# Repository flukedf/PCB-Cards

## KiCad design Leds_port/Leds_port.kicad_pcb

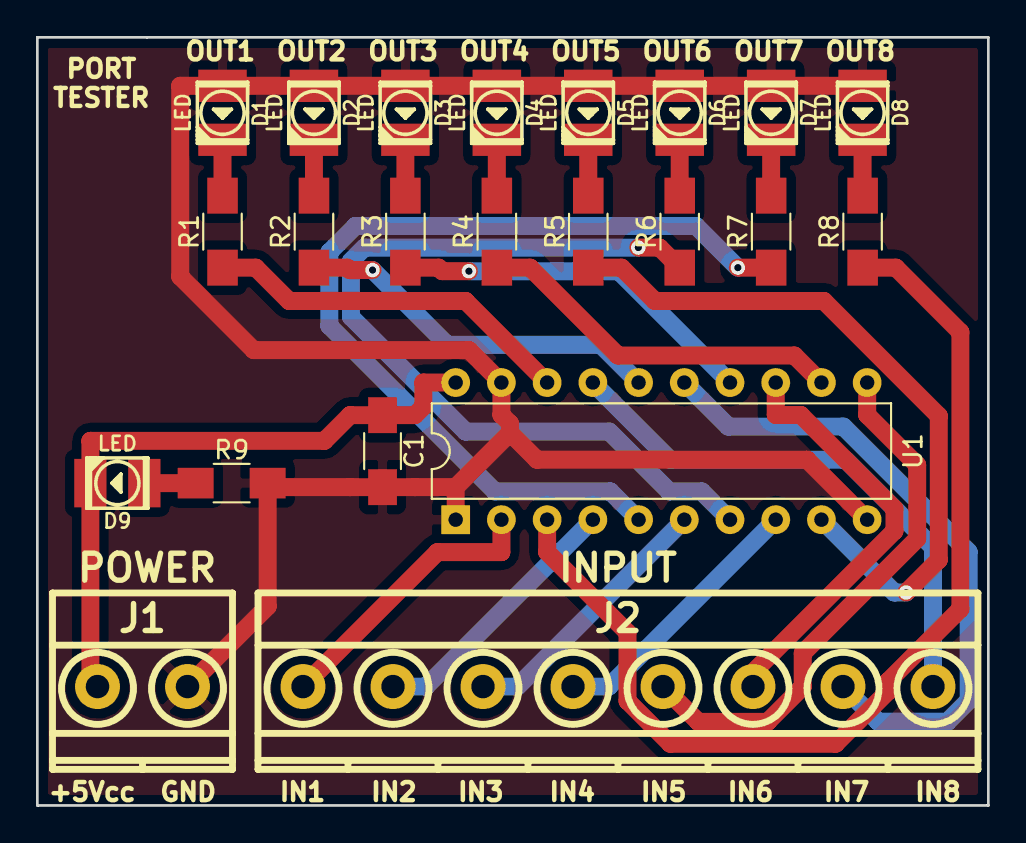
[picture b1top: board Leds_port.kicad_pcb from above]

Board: 2 copper layers, 52.8 x 42.7 mm, 22 parts (0 on the bottom side), 27 nets.

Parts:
C1: 100nF; C_1206_HandSoldering
D1, D2, D3, D4, D5, D6, D7, D8, D9: LED; Led_PLCC2_3528
J1: POWER; mkds_1,5-2
J2: INPUT; mkds_1,5-8
R1, R2, R3, R4, R5, R6, R7, R8, R9: 330; R_1206_HandSoldering
U1: 74LS244; DIP-20_W7.62mm

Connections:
+5Vcc: C1.1, D9.2, J1.1, U1.20
GND: C1.2, D1.1, D2.1, D3.1, D4.1, D5.1, D6.1, D7.1, D8.1, J1.2, R9.2, U1.1, U1.10, U1.19
IN01: J2.1, U1.2
IN02: J2.2, U1.4
IN03: J2.3, U1.6
IN04: J2.4, U1.8
IN05: J2.5, U1.11
IN06: J2.6, U1.13
IN07: J2.7, U1.15
IN08: J2.8, U1.17
unnamed: D1.2, R1.2
unnamed: D2.2, R2.2
unnamed: D3.2, R3.2
unnamed: D4.2, R4.2
unnamed: D5.2, R5.2
unnamed: D6.2, R6.2
unnamed: D7.2, R7.2
unnamed: D8.2, R8.2
unnamed: D9.1, R9.1
S1: R1.1, U1.18
S2: R2.1, U1.16
S3: R3.1, U1.14
S4: R4.1, U1.12
S5: R5.1, U1.9
S6: R6.1, U1.7
S7: R7.1, U1.5
S8: R8.1, U1.3

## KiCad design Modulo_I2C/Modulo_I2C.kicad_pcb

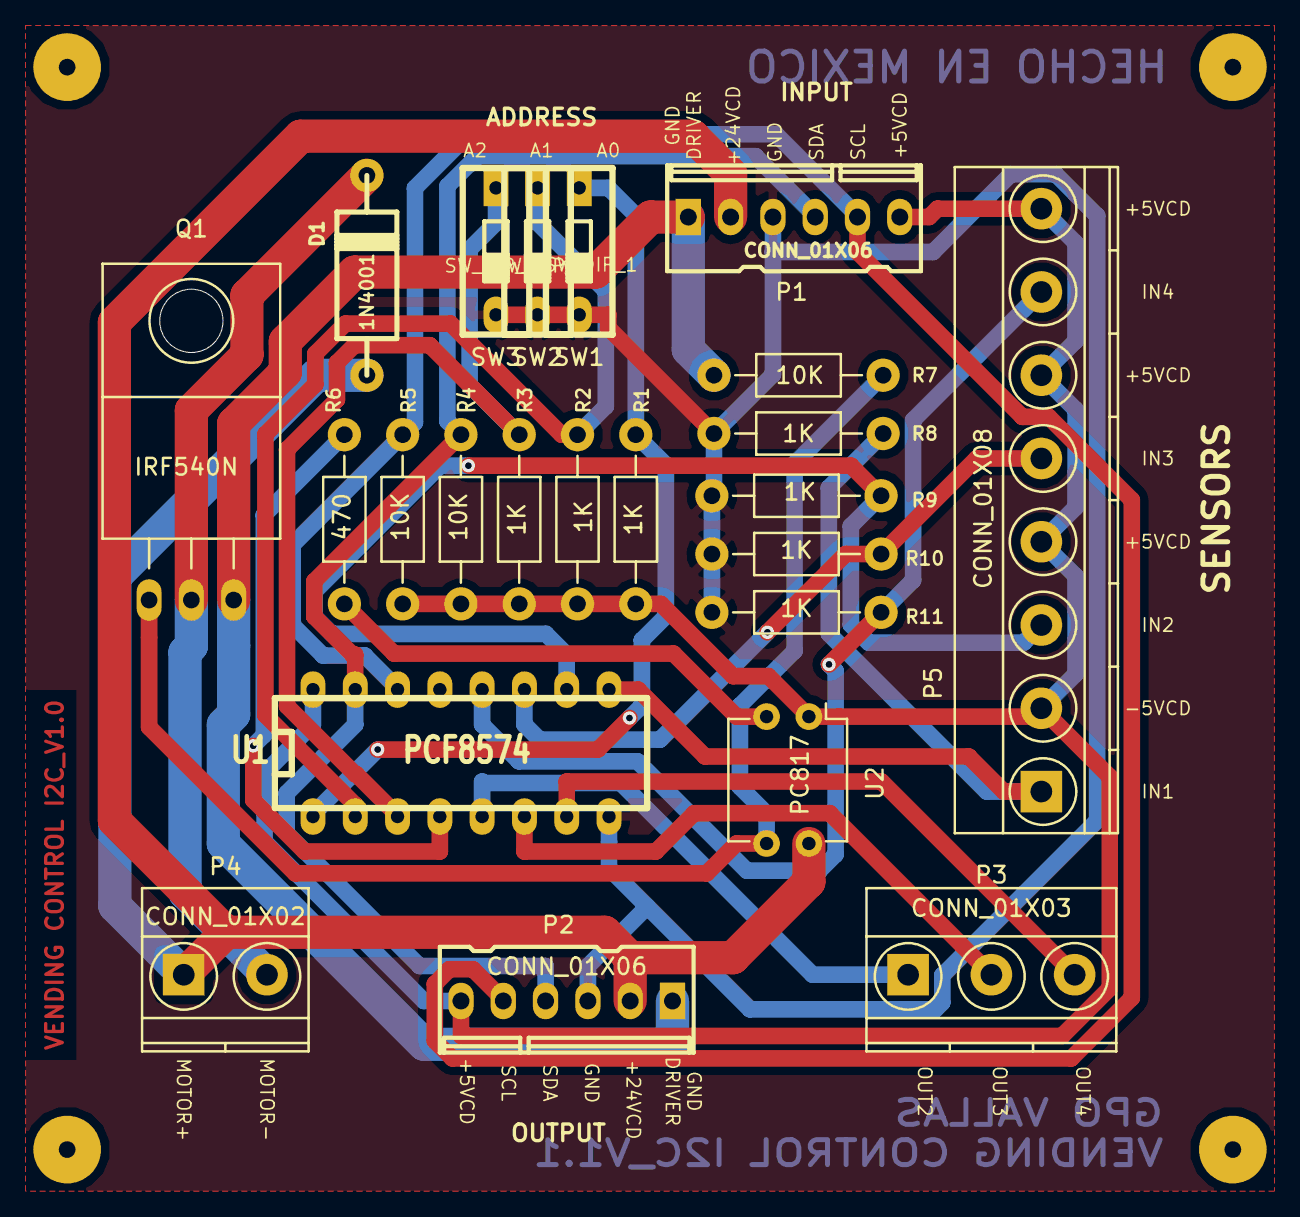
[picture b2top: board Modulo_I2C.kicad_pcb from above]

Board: 2 copper layers, 23 parts (0 on the bottom side), 20 nets.

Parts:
D1: 1N4001; diode_do15
P1, P2: CONN_01X06; kk100_22-23-2061
P3: CONN_01X03; TerminalBlock_Pheonix_MKDS1.5-3pol
P4: CONN_01X02; TerminalBlock_Pheonix_MKDS1.5-2pol
P5: CONN_01X08; TerminalBlock_Pheonix_MKDS1.5-8pol
Q1: IRF540N; TO-220_Neutral123_Horizontal
R1, R2, R3, R8, R9, R10, R11: 1K; Resistor_Horizontal_RM10mm
R4, R5, R7: 10K; Resistor_Horizontal_RM10mm
R6: 470; Resistor_Horizontal_RM10mm
SW1, SW2, SW3: SW_DIP_1; dip_1-300
U1: PCF8574; dil_16-300
U2: PC817; DIP-4_W7.62mm

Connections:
+5V: P1.6, P2.6, P5.2, P5.4, P5.6, P5.8, R1.1, R2.1, R3.1, R4.1, R5.1, U1.16, U2.1
+24VCD: D1.1, P1.2, P2.2, P4.1, U2.4
GND: P1.3, P2.3, R8.2, R9.2, R10.2, R11.2, SW1.2, SW2.2, SW3.2, U1.8
GND_DRIVER: P1.1, P2.1, Q1.3, R7.2
IN1: P5.1, R8.1, U1.9
IN2: P5.3, R9.1, U1.10
IN3: P5.5, R10.1, U1.11
IN4: P5.7, R11.1, U1.12
MOTOR-: D1.2, P4.2, Q1.2
unnamed: Q1.1, R7.1, U2.3
unnamed: R1.2, SW1.1, U1.1
unnamed: R2.2, SW2.1, U1.2
unnamed: R3.2, SW3.1, U1.3
unnamed: R6.1, U2.2
unnamed: R6.2, U1.4
OUT2: P3.1, U1.5
OUT3: P3.2, U1.6
OUT4: P3.3, U1.7
SCL: P1.5, P2.5, R5.2, U1.14
SDA: P1.4, P2.4, R4.2, U1.15

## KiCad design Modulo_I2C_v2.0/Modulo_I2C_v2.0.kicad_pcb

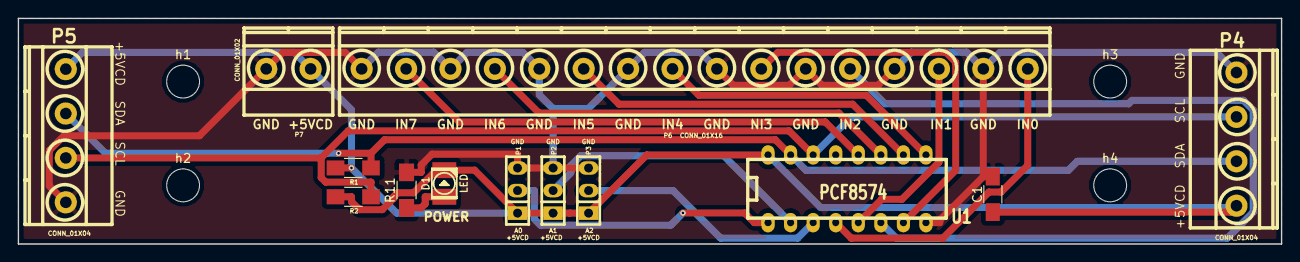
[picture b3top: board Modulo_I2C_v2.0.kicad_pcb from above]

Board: 2 copper layers, 142.2 x 25.4 mm, 17 parts (0 on the bottom side), 16 nets.

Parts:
C1: 100nF; C_1206_HandSoldering
D1: LED; Led_PLCC2_3528
P1, P2, P3: CONN_01X03; pin_strip_3
P4, P5: CONN_01X04; mkds_1,5-4
P6: CONN_01X16; mkds_1,5-16
P7: CONN_01X02; mkds_1,5-2
R1, R2: 10K; R_1206_HandSoldering
R11: 330; R_1206_HandSoldering
U1: PCF8574; dil_16-300
h1: h1; MountingHole_3.7mm
h2: h2; MountingHole_3.7mm
h3: h3; MountingHole_3.7mm
h4: h4; MountingHole_3.7mm

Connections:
+5V: C1.1, D1.2, P1.1, P2.1, P3.1, P4.1, P5.1, P7.1, R1.1, R2.1, U1.16
GND: C1.2, P1.3, P2.3, P3.3, P4.4, P5.4, P6.2, P6.4, P6.6, P6.8, P6.10, P6.12, P6.14, P6.16, P7.2, R11.2, U1.8
IN1: P6.1, U1.4
IN2: P6.3, U1.5
IN3: P6.5, U1.6
IN4: P6.7, U1.7
IN5: P6.9, U1.9
IN6: P6.11, U1.10
IN7: P6.13, U1.11
IN8: P6.15, U1.12
unnamed: D1.1, R11.1
unnamed: P1.2, U1.1
unnamed: P2.2, U1.2
unnamed: P3.2, U1.3
SCL: P4.3, P5.3, R2.2, U1.14
SDA: P4.2, P5.2, R1.2, U1.15

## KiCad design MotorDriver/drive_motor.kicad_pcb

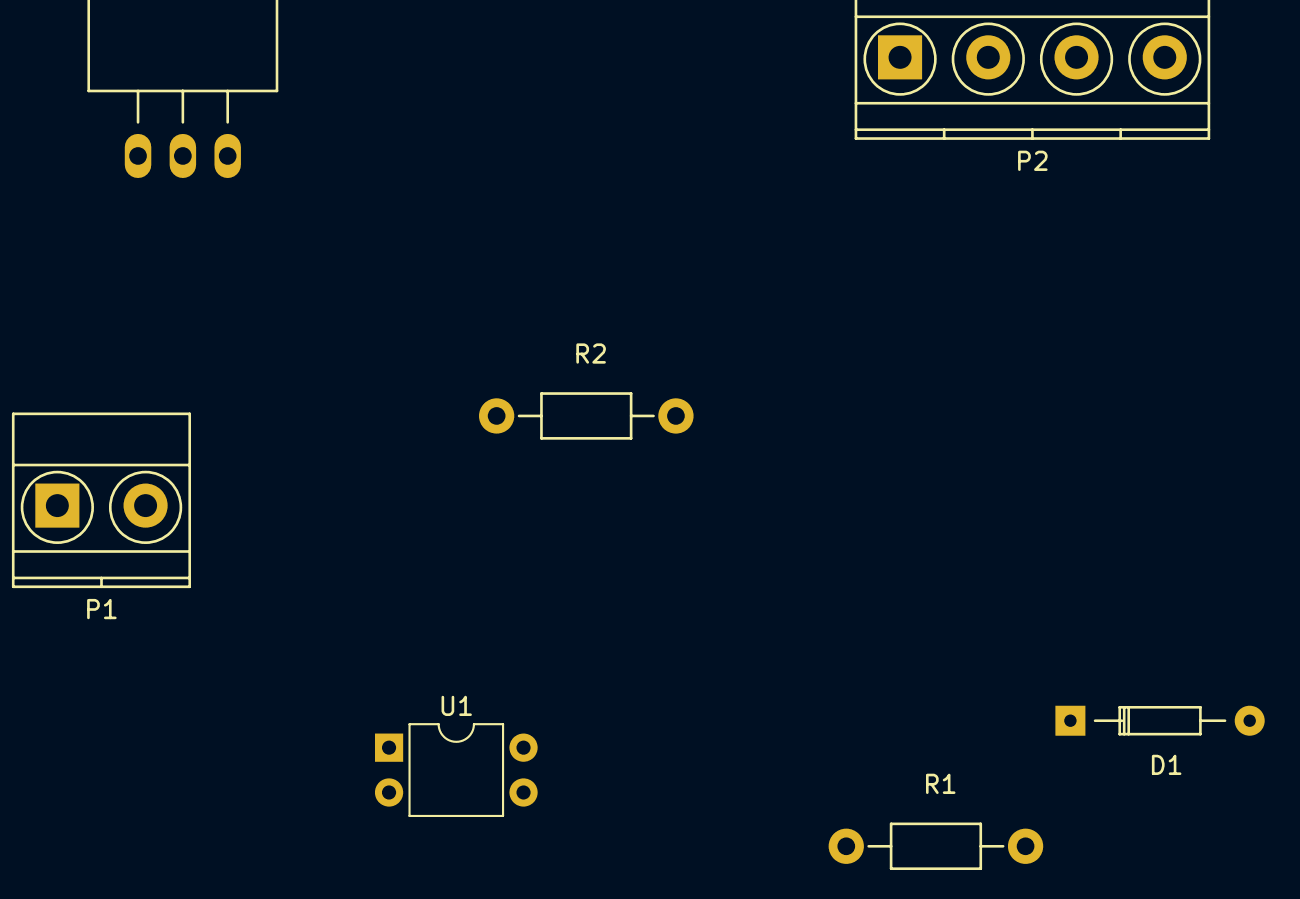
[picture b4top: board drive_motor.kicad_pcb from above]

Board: 2 copper layers, 7 parts (0 on the bottom side), 7 nets, no tracks yet.

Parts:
D1: D; Diode_DO-35_SOD27_Horizontal_RM10
P1: CONN_01X02; TerminalBlock_Pheonix_MKDS1.5-2pol
P2: CONN_01X04; TerminalBlock_Pheonix_MKDS1.5-4pol
Q1: IRF540N; TO-220_Neutral123_Horizontal
R1: 470; Resistor_Horizontal_RM10mm
R2: 10K; Resistor_Horizontal_RM10mm
U1: PC817; DIP-4_W7.62mm

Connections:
GND: P2.2, Q1.3, R2.2
GND_CTRL: P1.1, R1.2
MOTOR+: D1.1, P2.1, P2.3, U1.4
MOTOR-: D1.2, P2.4, Q1.2
unnamed: Q1.1, R2.1, U1.3
unnamed: R1.1, U1.2
SIGNAL: P1.2, U1.1

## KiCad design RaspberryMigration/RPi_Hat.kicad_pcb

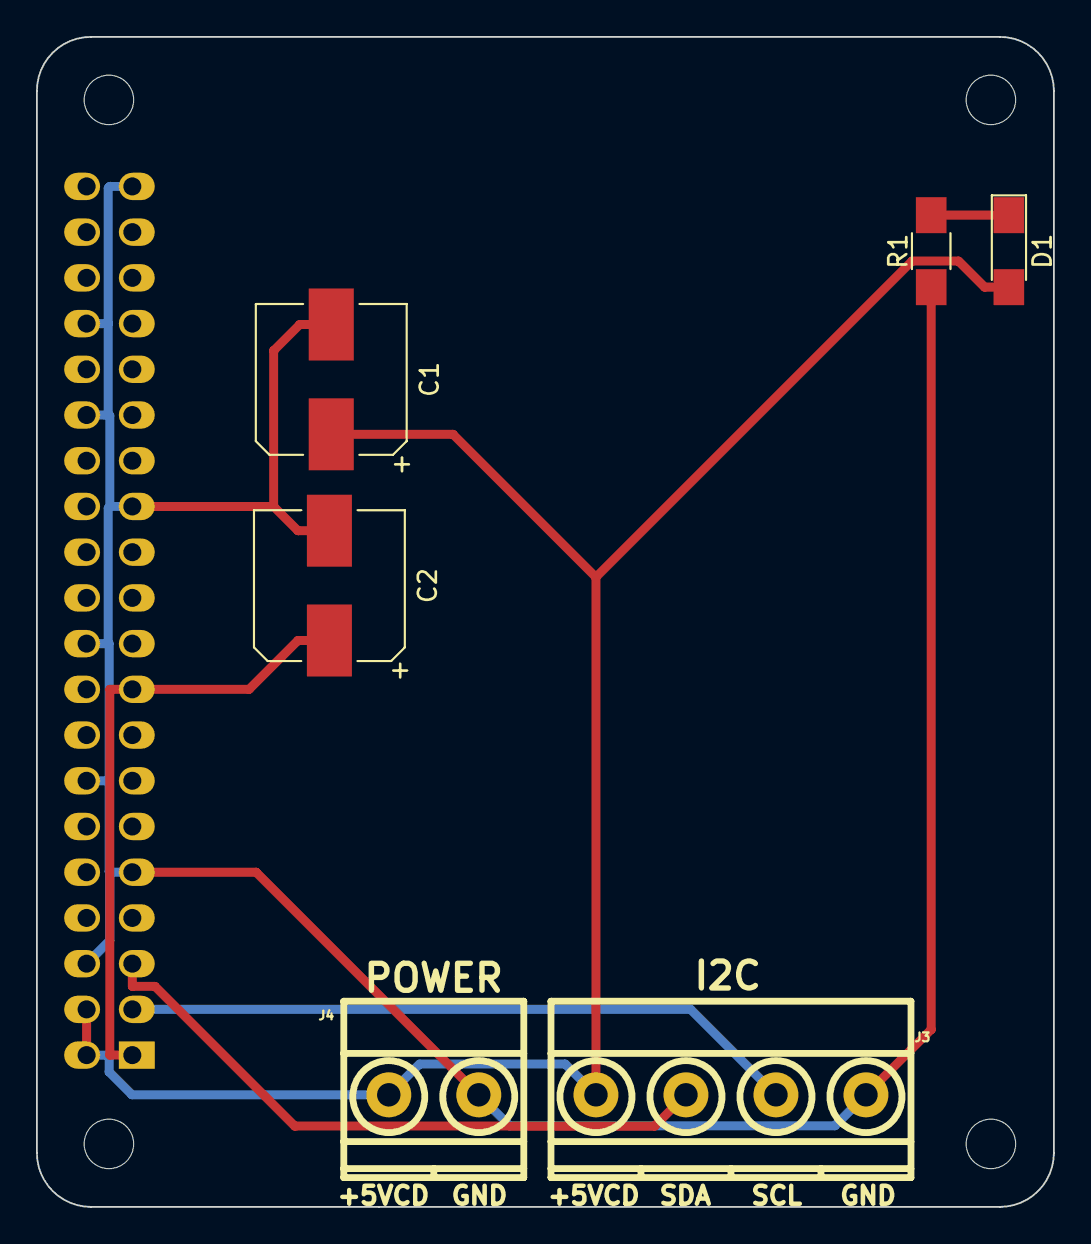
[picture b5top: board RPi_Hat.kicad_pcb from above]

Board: 2 copper layers, 56.5 x 65.0 mm, 11 parts (1 on the bottom side), 6 nets.

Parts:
C1: C5V 10uf; CP_Elec_8x5.4
C2: C3V 10uf; CP_Elec_8x5.4
D1: LED_ALT; LED_1206_HandSoldering
J1: RPi_GPIO; pin_socket_20x2_mirror
J3: I2C; mkds_1,5-4
J4: POWER; mkds_1,5-2
R1: R; R_1206_HandSoldering
h1, h2, h3, h4: RPi_Hat_Mounting_Hole

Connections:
+3V3: C2.1, J1.1, J1.17
+5V: C1.1, D1.2, J1.2, J1.4, J3.1, J4.1
/RPi_GPIO/SCL: J1.3, J3.3
/RPi_GPIO/SDA: J1.5, J3.2
GND: C1.2, C2.2, J1.6, J1.9, J1.14, J1.20, J1.25, J1.30, J1.34, J1.39, J3.4, J4.2, R1.1
unnamed: D1.1, R1.2

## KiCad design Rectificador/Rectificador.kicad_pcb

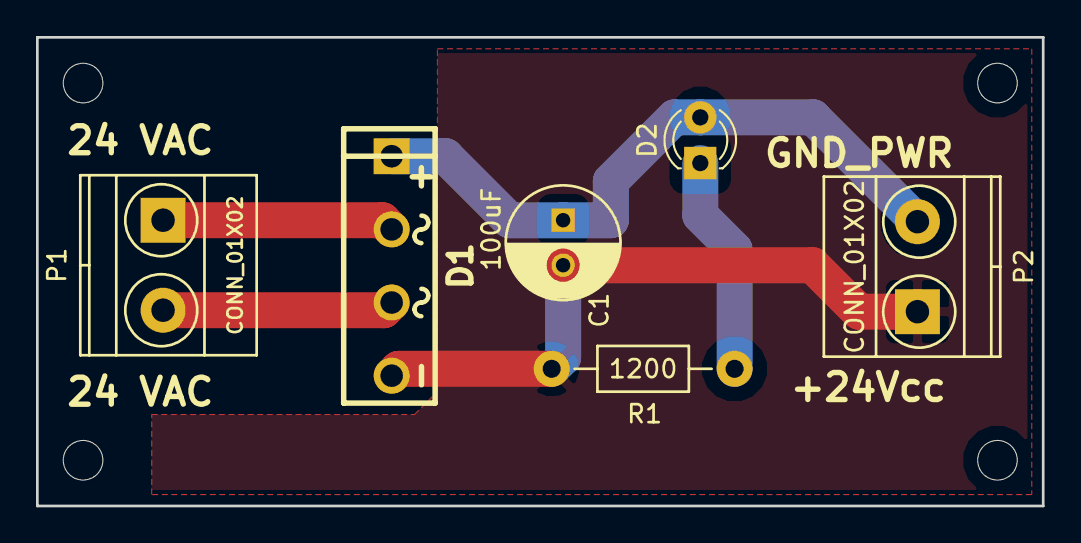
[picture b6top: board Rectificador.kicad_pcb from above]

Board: 2 copper layers, 55.9 x 26.0 mm, 6 parts (0 on the bottom side), 5 nets.

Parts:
C1: 100uF; C_Radial_D6.3_L11.2_P2.5
D1: KPB206; bridge_2KBP
D2: LED; LED_D3.0mm
P1, P2: CONN_01X02; TerminalBlock_Pheonix_MKDS1.5-2pol
R1: 1200; Resistor_Horizontal_RM10mm

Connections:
+24V: C1.1, D1.1, D2.2, P2.2
GNDPWR: C1.2, D1.4, P2.1, R1.2
unnamed: D1.2, P1.1
unnamed: D1.3, P1.2
unnamed: D2.1, R1.1

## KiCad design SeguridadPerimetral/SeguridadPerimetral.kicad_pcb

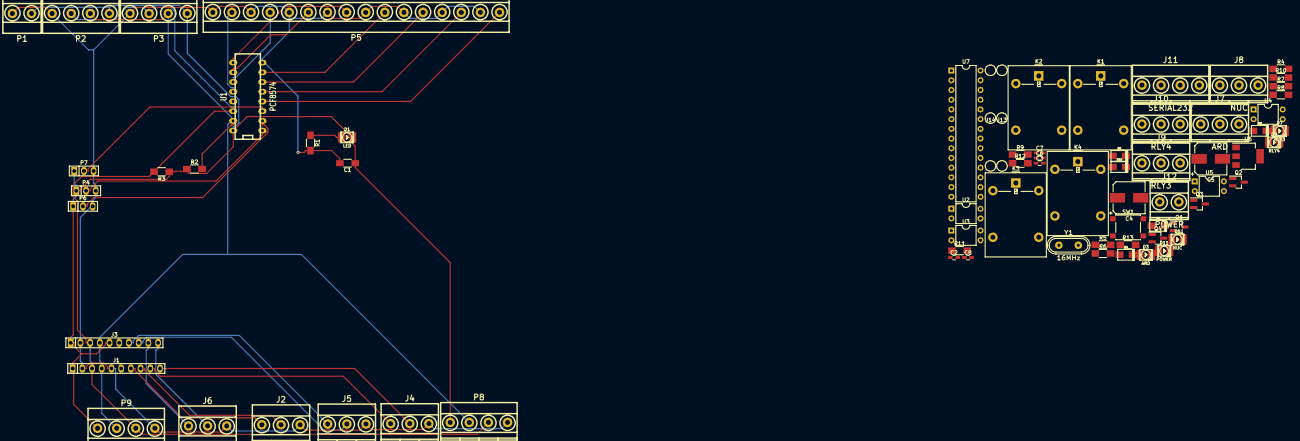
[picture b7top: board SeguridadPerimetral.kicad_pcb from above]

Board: 2 copper layers, 72 parts (0 on the bottom side), 69 nets.

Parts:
C1: 100nF; C_1206_HandSoldering
C2, C6: 22pF; C_0603_HandSoldering
C3, C8: 100nF; C_0603_HandSoldering
C4, C5: 47uF; CP_Elec_8x6.5
C7: 0.1uF; C_0603_HandSoldering
D1: LED; Led_PLCC2_3528
D2, D4, D6, D8, D10: 1N4001; do214ac
D3: ARD; Led_PLCC2_3528
D5: NUC; Led_PLCC2_3528
D7: RLY3; Led_PLCC2_3528
D9: RLY4; Led_PLCC2_3528
D11: POWER; Led_PLCC2_3528
J1, J3: CONN_01X10; pin_socket_10
J2, J4, J5, J6: CONN_01X03; mkds_1,5-3
J7: ARD; mkds_1,5-3
J8: NUC; mkds_1,5-3
J9: RLY3; mkds_1,5-3
J10: RLY4; mkds_1,5-3
J11: SERIAL232; mkds_1,5-4
J12: POWER; mkds_1,5-2
J13, J14: hole; Bracket_RielDin_hole
K1, K2, K3, K4: JS1-5V-F
P1: CONN_01X02; mkds_1,5-2
P2, P3, P8, P9: CONN_01X04; mkds_1,5-4
P4, P6, P7: CONN_01X03; pin_strip_3
P5: CONN_01X16; mkds_1,5-16
Q1, Q2, Q3, Q4: MMBT5551L; SOT-23_Handsoldering
R1, R12: 330; R_1206_HandSoldering
R2, R3, R4, R5, R8, R9, R13: 10K; R_1206_HandSoldering
R6, R7, R10, R11: 1K; R_1206_HandSoldering
SW1: RESET; SW_SPST_PTS645
U1: PCF8574; dil_16-300
U2, U3, U4, U5: PC817; DIP-4_W7.62mm
U6: AMS1117-5.0; SOT-223-3Lead_TabPin2
U7: ATmega328P-PU; DIP-28_W7.62mm
Y1: 16MHz; crystal_hc-49s

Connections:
+5V: C1.1, C3.1, C5.1, C8.1, D1.2, D2.1, D4.1, D6.1, D8.1, D11.1, J1.1, J3.1, J3.5, K1.2, K2.2, K3.2, K4.2, P1.1, P2.1, P3.1, P4.1, P6.1, P7.1, P8.1, P9.1, R2.1, R3.1, R13.1, U1.16, U2.4, U3.4, U4.4, U5.4, U6.2, U7.7, U7.20
+12V: C4.1, D10.1, U6.3
A0: J1.7, J2.1
A1: J1.8, J2.2
A2: J1.9, J4.1
A3: J1.10, J4.2
B0: J3.7, J5.1
B1: J3.8, J5.2
B2: J3.9, J6.1
B3: J3.10, J6.2
D4: D5.2, U7.6
D5: D3.2, U7.11
D6: D9.2, U7.12
D7: D7.2, U7.13
DTR: C7.1, J11.1
GND: C1.2, C2.1, C3.2, C4.2, C5.2, C6.1, C8.2, J1.2, J1.5, J2.3, J3.2, J4.3, J5.3, J6.3, J11.4, J12.1, P1.2, P2.4, P3.4, P4.3, P5.2, P5.4, P5.6, P5.8, P5.10, P5.12, P5.14, P5.16, P6.3, P7.3, P8.4, P9.4, Q1.2, Q2.2, Q3.2, Q4.2, R1.2, R6.1, R7.1, R10.1, R11.1, R12.2, SW1.2, U1.8, U6.1, U7.8, U7.22
IN1: P5.1, U1.4
IN2: P5.3, U1.5
IN3: P5.5, U1.6
IN4: P5.7, U1.7
IN5: P5.9, U1.9
IN6: P5.11, U1.10
IN7: P5.13, U1.11
IN8: P5.15, U1.12
unnamed: C2.2, U7.9, Y1.1
unnamed: C6.2, U7.10, Y1.2
unnamed: C7.2, R13.2, SW1.1, U7.1
unnamed: D1.1, R1.1
unnamed: D2.2, K1.5, Q1.3
unnamed: D3.1, U2.1
unnamed: D4.2, K2.5, Q2.3
unnamed: D5.1, U3.1
unnamed: D6.2, K3.5, Q3.3
unnamed: D7.1, U4.1
unnamed: D8.2, K4.5, Q4.3
unnamed: D9.1, U5.1
unnamed: D10.2, J12.2
unnamed: D11.2, R12.1
unnamed: J7.1, K1.3
unnamed: J7.2, K1.1
unnamed: J7.3, K1.4
unnamed: J8.1, K2.3
unnamed: J8.2, K2.1
unnamed: J8.3, K2.4
unnamed: J9.1, K3.3
unnamed: J9.2, K3.1
unnamed: J9.3, K3.4
unnamed: J10.1, K4.3
unnamed: J10.2, K4.1
unnamed: J10.3, K4.4
unnamed: P4.2, U1.1
unnamed: P6.2, U1.2
unnamed: P7.2, U1.3
unnamed: Q1.1, R4.2
unnamed: Q2.1, R5.2
unnamed: Q3.1, R8.2
unnamed: Q4.1, R9.2
unnamed: R4.1, U2.3
unnamed: R5.1, U3.3
unnamed: R6.2, U2.2
unnamed: R7.2, U3.2
unnamed: R8.1, U4.3
unnamed: R9.1, U5.3
unnamed: R10.2, U4.2
unnamed: R11.2, U5.2
Rx: J11.2, U7.2
SCL: J1.3, J3.3, P2.3, P3.3, P8.3, P9.3, R3.2, U1.14
SDA: J1.4, J3.4, P2.2, P3.2, P8.2, P9.2, R2.2, U1.15
Tx: J11.3, U7.3
